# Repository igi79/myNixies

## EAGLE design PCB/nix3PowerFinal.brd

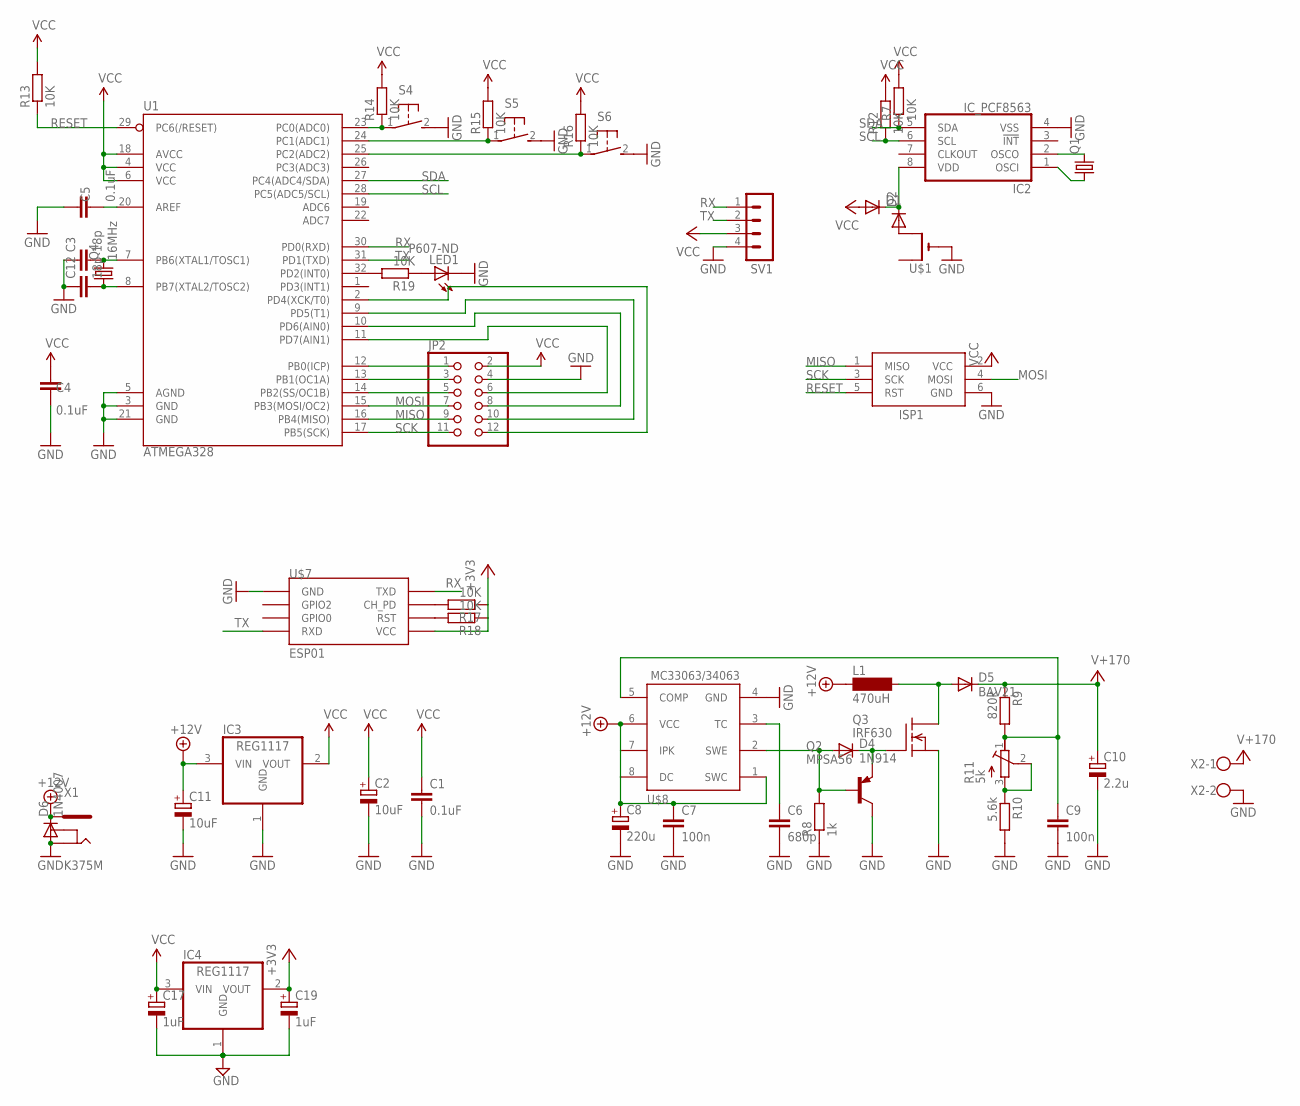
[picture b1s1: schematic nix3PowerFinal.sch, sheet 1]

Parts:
C1, C4, C5: 0.1uF; C0805
C2, C11: 10uF; E2,5-5
C3, C12: 18p; C0805
C6: 680p; C050-025X075
C7, C9: 100n; C050-025X075
C8: 220u; E3,5-8
C10: 2.2u; E3,5-8
C17, C19: 1uF; 153CLV-0505
D1, D2: DIODE-SOD80C; SOD80C
D4: 1N914; D-5
D5: BAV21; D-5
D6: 1N4007; D-7.5
IC2: IC_PCF8563; SO-8
IC3, IC4: REG1117; SOT223
ISP1: AVRISP-6; AVRISP
JP2: PINHD-2X6; 2X06
L1: 470uH; BS11
LED1: P607-ND; Q62902-B155
Q1: CRYSTALTC38H; TC38H
Q2: MPSA56; TO92-CBE
Q3: IRF630; TO220
Q4: 16MHz; HC49U-V
R7, R12, R13, R14, R15, R16, R17, R18, R19: 10K; R0805
R8: 1k; 0204/5
R9: 820k; 0204/5
R10: 5.6k; 0204/5
R11: 5k; RTRIM43P
S4, S5, S6: 31-XX; B3F-31XX
SV1: MA04-1
U1: ATMEGA328; TQFP32-08
U$1: CR2032THM; CR2032-THRU
U$7: ESP01
U$8: MC33063/MC34063P; DIL08
X1: K375M
X2: W237-102

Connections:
+3V3: C19.+, IC4.2 (VOUT), R17.1, R18.1, U$7.VCC
+12V: C7.1, C8.+, C11.+, D6.C, IC3.3 (VIN), L1.1, U$8.1 (SWC), U$8.6 (VCC), U$8.7 (IPK), U$8.8 (DC), X1.1
GND: C1.2, C2.-, C3.1, C4.1, C5.2, C6.2, C7.2, C8.-, C9.2, C10.-, C11.-, C12.1, C17.-, C19.-, D6.A, IC2.4 (VSS), IC3.1 (GND), IC4.1 (GND), ISP1.6 (GND), JP2.4, LED1.K (C), Q2.C, Q3.3 (S), R8.1, R10.2, S4.2 (S), S5.2 (S), S6.2 (S), SV1.4, U1.3 (GND), U1.5 (AGND), U1.21 (GND), U$1.-, U$7.GND, U$8.4 (GND), X1.2, X2.2
MISO: ISP1.1 (MISO), JP2.9, U1.16 (PB4(MISO))
MOSI: ISP1.4 (MOSI), JP2.7, U1.15 (PB3(MOSI/OC2))
unnamed: IC2.2 (OSCO), Q1.2
unnamed: D2.A, U$1.+2 (+1)
unnamed: C6.1, U$8.3 (TC)
unnamed: JP2.5, U1.14 (PB2(SS/OC1B))
unnamed: JP2.3, U1.13 (PB1(OC1A))
unnamed: JP2.1, U1.12 (PB0(ICP))
unnamed: IC2.1 (OSCI), Q1.1
unnamed: D1.C, D2.C, IC2.8 (VDD)
unnamed: C3.2, Q4.2, U1.7 (PB6(XTAL1/TOSC1))
unnamed: C12.2, Q4.1, U1.8 (PB7(XTAL2/TOSC2))
unnamed: R19.2, U1.32 (PD2(INT0))
unnamed: LED1.A, R19.1
unnamed: R17.2, U$7.CH_PD
unnamed: R18.2, U$7.RST
unnamed: JP2.12, U1.2 (PD4(XCK/T0))
unnamed: JP2.6, U1.11 (PD7(AIN1))
unnamed: D4.C, Q2.E, Q3.1 (G)
unnamed: D5.A, L1.2, Q3.2 (D)
unnamed: D4.A, Q2.B, R8.2, U$8.2 (SWE)
unnamed: C9.1, R9.2, R11.1 (A), U$8.5 (COMP)
unnamed: R10.1, R11.2 (S), R11.3 (E)
unnamed: C5.1, U1.20 (AREF)
unnamed: JP2.8, U1.10 (PD6(AIN0))
unnamed: JP2.10, U1.9 (PD5(T1))
unnamed: R14.1, S4.1, U1.23 (PC0(ADC0))
unnamed: R15.1, S5.1, U1.24 (PC1(ADC1))
unnamed: R16.1, S6.1, U1.25 (PC2(ADC2))
RESET: ISP1.5 (RST), R13.1, U1.29 (PC6(/RESET))
RX: SV1.1, U1.30 (PD0(RXD)), U$7.TX (TXD)
SCK: ISP1.3 (SCK), JP2.11, U1.17 (PB5(SCK))
SCL: IC2.6 (SCL), R12.1, U1.28 (PC5(ADC5/SCL))
SDA: IC2.5 (SDA), R7.1, U1.27 (PC4(ADC4/SDA))
TX: SV1.2, U1.31 (PD1(TXD)), U$7.RX (RXD)
V+: C10.+, D5.C, R9.1, X2.1
VCC: C1.1, C2.+, C4.2, C17.+, D1.A, IC3.2 (VOUT), IC4.3 (VIN), ISP1.2 (VCC), JP2.2, R7.2, R12.2, R13.2, R14.2, R15.2, R16.2, SV1.3, U1.4 (VCC), U1.6 (VCC), U1.18 (AVCC)

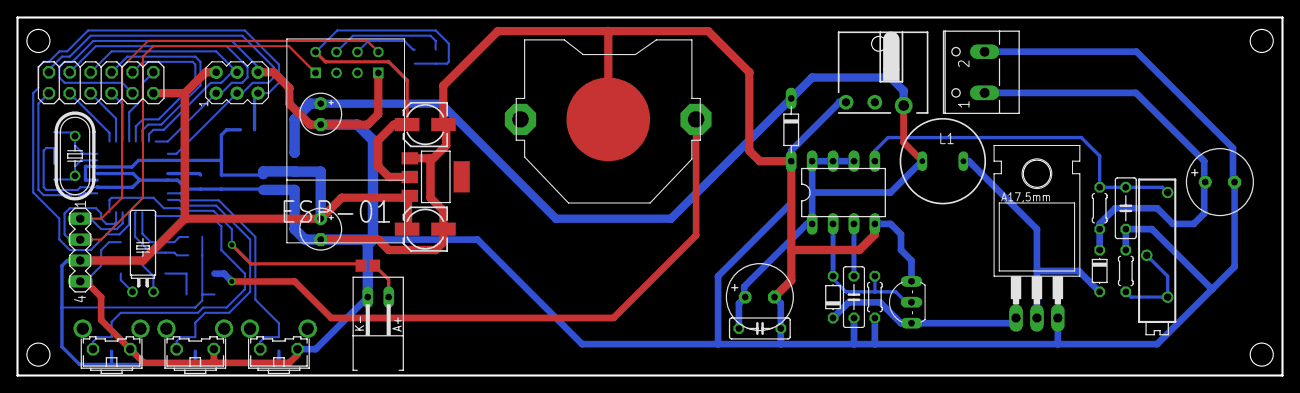
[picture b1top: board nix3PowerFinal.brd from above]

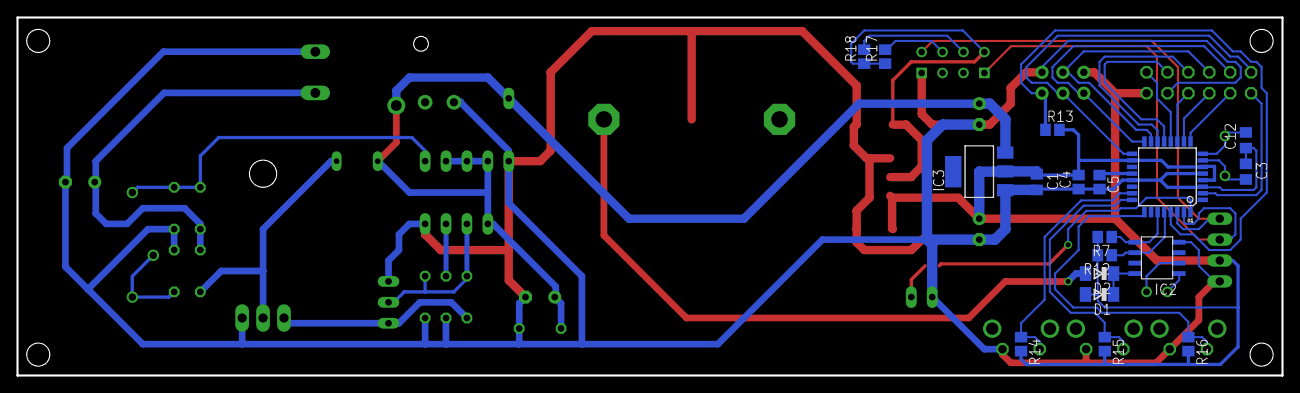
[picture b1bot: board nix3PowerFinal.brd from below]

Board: 2 copper layers, 153.7 x 43.5 mm, 53 parts (18 on the bottom side), 40 nets.

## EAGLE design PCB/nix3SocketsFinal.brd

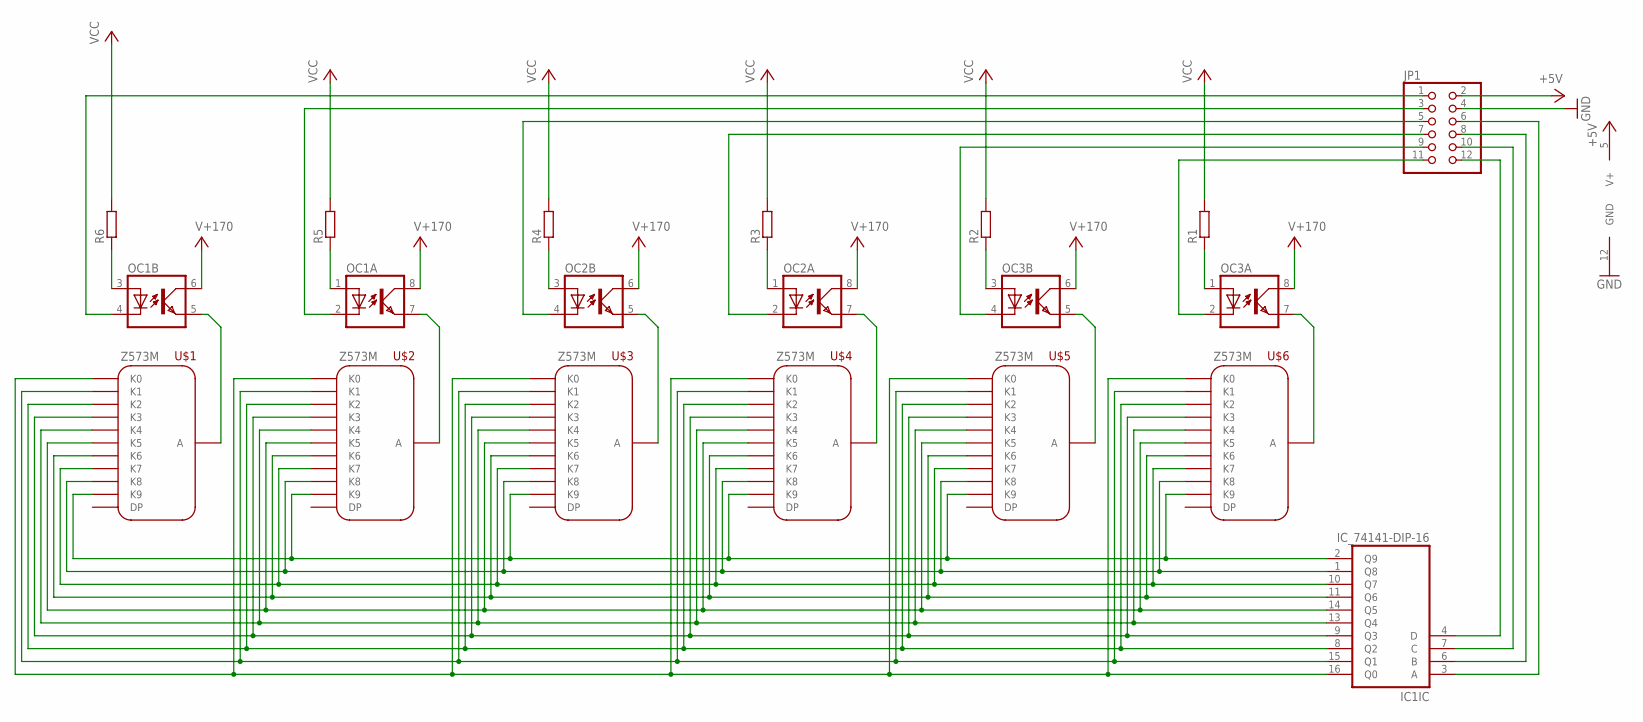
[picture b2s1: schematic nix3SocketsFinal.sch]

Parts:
IC1: IC_74141-DIP-16; DIL16
JP1: PINHD-2X6; 2X06
OC1, OC2, OC3: ILD621; DIL08
R1, R2, R3, R4, R5, R6: R-EU_R0805W; R0805W
U$1, U$2, U$3, U$4, U$5, U$6: Z573M

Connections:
+5V: IC1.5 (V+), JP1.2, R1.2, R2.2, R3.2, R4.2, R5.2, R6.2
GND: IC1.12 (GND), JP1.4
unnamed: IC1.2 (Q9), U$1.K9, U$2.K9, U$3.K9, U$4.K9, U$5.K9, U$6.K9
unnamed: IC1.1 (Q8), U$1.K8, U$2.K8, U$3.K8, U$4.K8, U$5.K8, U$6.K8
unnamed: IC1.10 (Q7), U$1.K7, U$2.K7, U$3.K7, U$4.K7, U$5.K7, U$6.K7
unnamed: IC1.11 (Q6), U$1.K6, U$2.K6, U$3.K6, U$4.K6, U$5.K6, U$6.K6
unnamed: IC1.14 (Q5), U$1.K5, U$2.K5, U$3.K5, U$4.K5, U$5.K5, U$6.K5
unnamed: IC1.13 (Q4), U$1.K4, U$2.K4, U$3.K4, U$4.K4, U$5.K4, U$6.K4
unnamed: IC1.9 (Q3), U$1.K3, U$2.K3, U$3.K3, U$4.K3, U$5.K3, U$6.K3
unnamed: IC1.8 (Q2), U$1.K2, U$2.K2, U$3.K2, U$4.K2, U$5.K2, U$6.K2
unnamed: IC1.15 (Q1), U$1.K1, U$2.K1, U$3.K1, U$4.K1, U$5.K1, U$6.K1
unnamed: OC3.7 (EMIT), U$6.A
unnamed: IC1.16 (Q0), U$1.K0, U$2.K0, U$3.K0, U$4.K0, U$5.K0, U$6.K0
unnamed: OC1.5 (EMIT), U$1.A
unnamed: OC1.7 (EMIT), U$2.A
unnamed: OC2.5 (EMIT), U$3.A
unnamed: OC2.7 (EMIT), U$4.A
unnamed: OC3.5 (EMIT), U$5.A
unnamed: JP1.11, OC3.2 (C)
unnamed: JP1.9, OC3.4 (C)
unnamed: JP1.7, OC2.2 (C)
unnamed: JP1.5, OC2.4 (C)
unnamed: JP1.3, OC1.2 (C)
unnamed: JP1.1, OC1.4 (C)
unnamed: IC1.4 (D), JP1.12
unnamed: IC1.7 (C), JP1.10
unnamed: IC1.6 (B), JP1.8
unnamed: IC1.3 (A), JP1.6
unnamed: OC1.3 (A), R6.1
unnamed: OC1.1 (A), R5.1
unnamed: OC2.3 (A), R4.1
unnamed: OC2.1 (A), R3.1
unnamed: OC3.3 (A), R2.1
unnamed: OC3.1 (A), R1.1
V+: OC1.6 (COL), OC1.8 (COL), OC2.6 (COL), OC2.8 (COL), OC3.6 (COL), OC3.8 (COL)

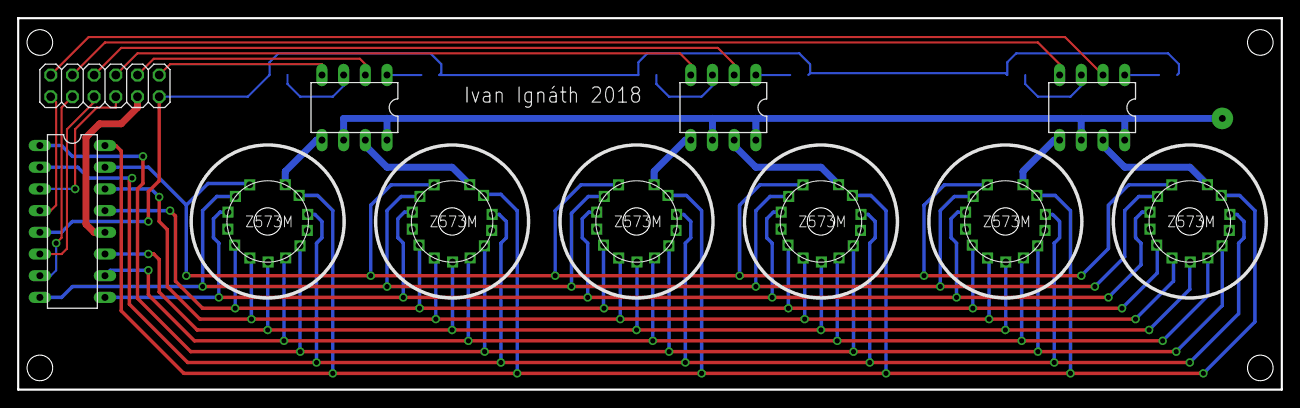
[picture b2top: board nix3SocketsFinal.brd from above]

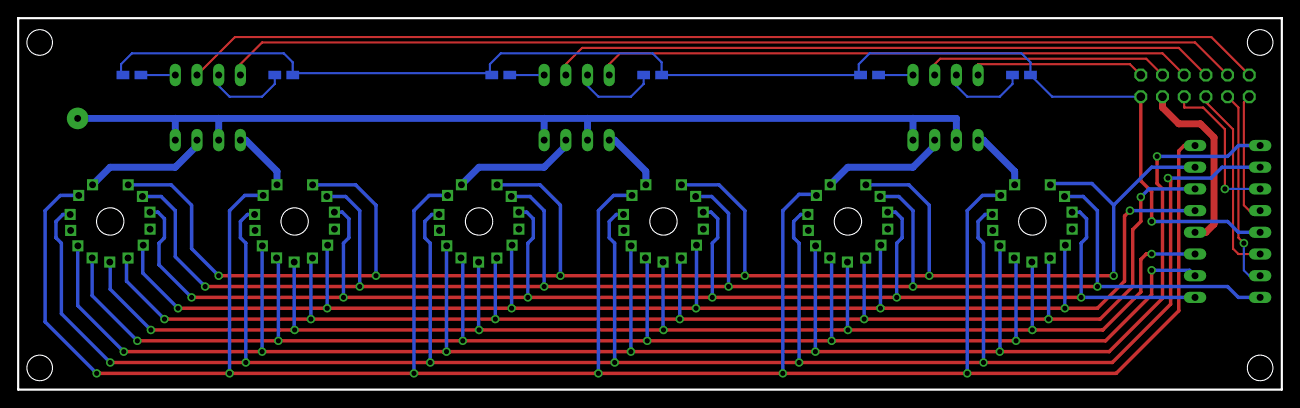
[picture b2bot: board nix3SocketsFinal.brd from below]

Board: 2 copper layers, 147.9 x 43.5 mm, 17 parts (6 on the bottom side), 35 nets.

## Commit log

2019-01-20 init
2019-02-20 Fix pcb
